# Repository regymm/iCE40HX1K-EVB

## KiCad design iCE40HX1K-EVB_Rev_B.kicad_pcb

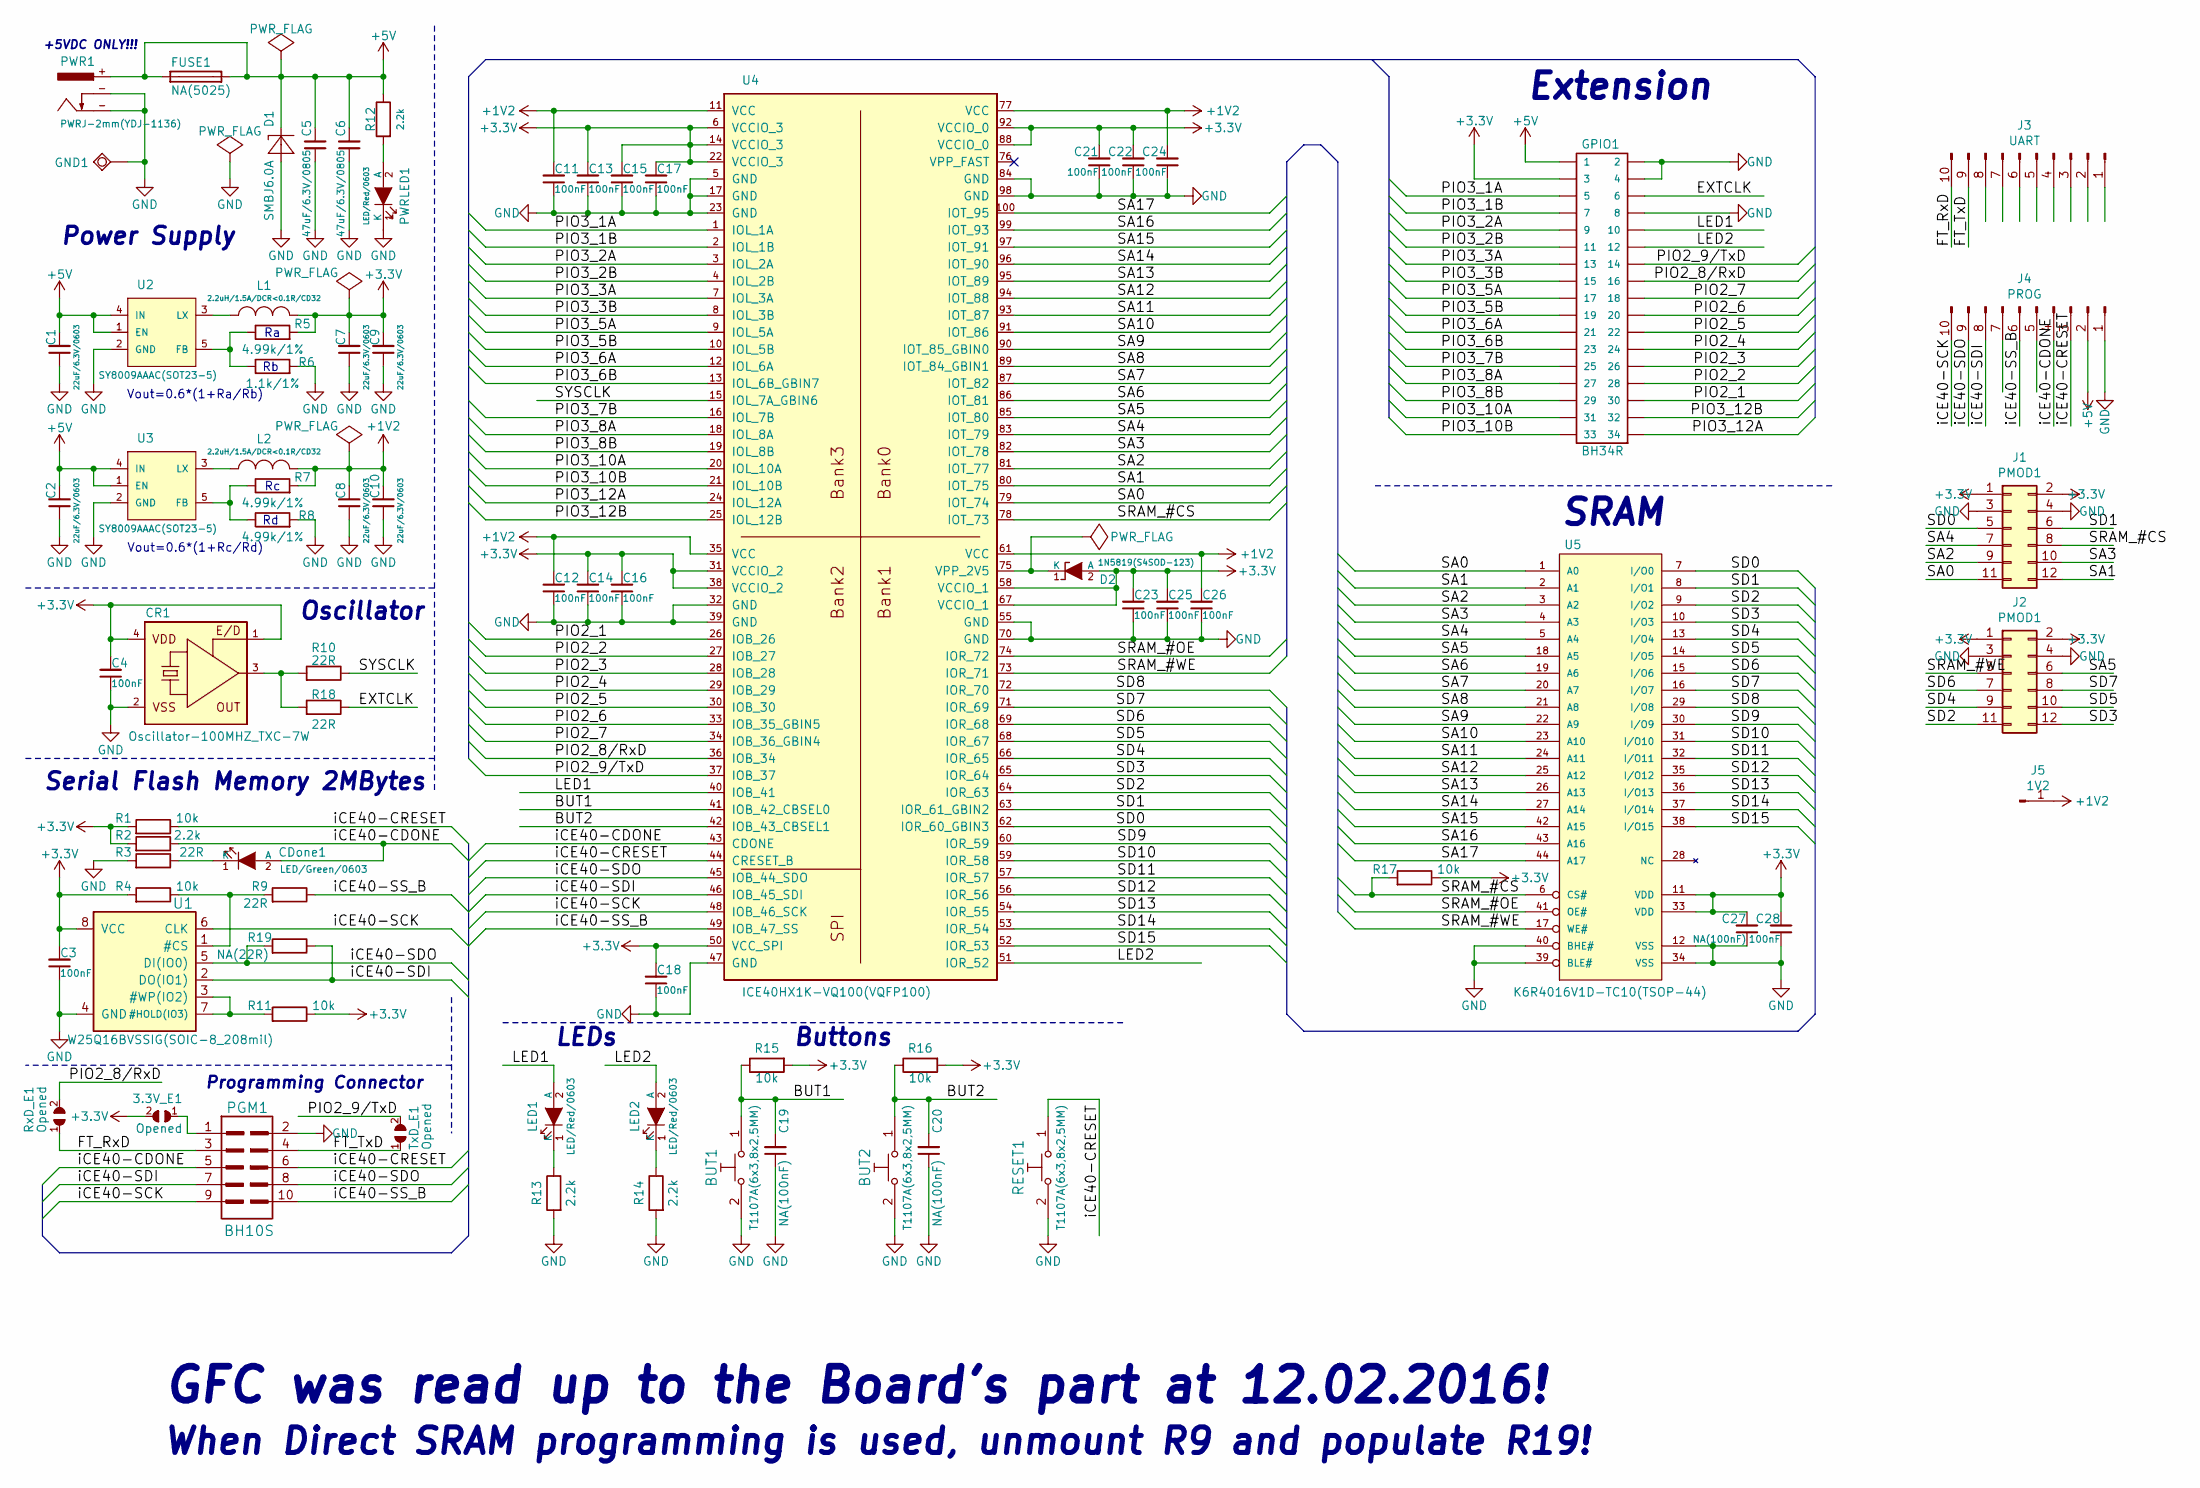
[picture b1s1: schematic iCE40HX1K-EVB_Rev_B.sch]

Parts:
3.3V_E1: Opened; SJ
BUT1, BUT2: T1107A(6x3,8x2,5MM)
C1, C2, C7, C8, C9, C10: 22uF/6.3V/0603; C_0603_5MIL_DWS
C3, C4, C11, C12, C13, C14, C15, C16, C17, C18, C21, C22, C23, C24, C25, C26, C28: 100nF; C_0402_5MIL_DWS
C5, C6: 47uF/6.3V/0805; C_0805_5MIL_DWS
C19, C20, C27: NA(100nF); C_0402_5MIL_DWS
CDone1: LED/Green/0603; LED_0603_KA
CR1: Oscillator-100MHZ_TXC-7W; Crystal_SMD_3225-4Pin_3.2x2.5mm_HandSoldering
D1: SMBJ6.0A; DO214AA
D2: 1N5819(S4SOD-123); SOD-123_1C-2A_KA
FUSE1: NA(5025); FUSE-5025
GND1: TESTPAD; TEST_PAD40x70_SQUARE
GPIO1: BH34R
J1, J2: PMOD1; PinHeader_2x06_P2.54mm_Vertical
J3: UART; PinHeader_1x10_P2.54mm_Vertical
J4: PROG; PinHeader_1x10_P2.54mm_Vertical
J5: 1V2; PinHeader_1x01_P2.54mm_Vertical
L1, L2: 2.2uH/1.5A/DCR<0.1R/CD32; CD32
LED1, LED2: LED/Red/0603; LED_0603_KA
PGM1: BH10S; UEXT_ML10
PWR1: PWRJ-2mm(YDJ-1136)
PWRLED1: LED/Red/0603; LED_0603_KA
R1, R4, R11, R15, R16, R17: 10k; R_0402_5MIL_DWS
R2, R12, R13, R14: 2.2k; R_0402_5MIL_DWS
R3, R9, R10, R18: 22R; R_0402_5MIL_DWS
R5, R7, R8: 4.99k/1%; R_0402_5MIL_DWS
R6: 1.1k/1%; R_0402_5MIL_DWS
R19: NA(22R); R_0402_5MIL_DWS
RESET1: T1107A(6x3,8x2,5MM)
RxD_E1: Opened; SJ
TxD_E1: Opened; SJ
U1: W25Q16BVSSIG(SOIC-8_208mil); SO-8_208mil
U2, U3: SY8009AAAC(SOT23-5); SOT-23-5
U4: ICE40HX1K-VQ100(VQFP100); VQFP100_Pitch-0.5mm_Dimensions-16.00x16.00x1.20mm
U5: K6R4016V1D-TC10(TSOP-44); TSOP-44_Pitch-0.80mm_18.80x11.80x1.20mm

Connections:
+1V2: C8.2, C10.2, C11.2, C12.2, C24.2, C26.2, J5.1, L2.1, R7.2, U4.11 (VCC), U4.35 (VCC), U4.61 (VCC), U4.77 (VCC)
+3V3: 3.3V_E1.2, C3.2, C4.2, C7.2, C9.2, C13.2, C14.2, C15.2, C16.2, C17.2, C18.2, C21.2, C22.2, C23.2, C25.2, C27.2, C28.2, CR1.1 (E/D), CR1.4 (VDD), D2.2 (A), GPIO1.3, J1.1, J1.2, J2.1, J2.2, L1.1, R1.2, R2.2, R4.2, R5.2, R11.1, R15.2, R16.2, R17.1, U1.8 (VCC), U4.6 (VCCIO_3), U4.14 (VCCIO_3), U4.22 (VCCIO_3), U4.31 (VCCIO_2), U4.38 (VCCIO_2), U4.50 (VCC_SPI), U4.58 (VCCIO_1), U4.67 (VCCIO_1), U4.88 (VCCIO_0), U4.92 (VCCIO_0), U5.11 (VDD), U5.33 (VDD)
+5V: C1.2, C2.2, C5.2, C6.2, D1.C, FUSE1.1, FUSE1.2, GPIO1.1, J4.2, PWR1.+, R12.1, U2.1 (EN), U2.4 (IN), U3.1 (EN), U3.4 (IN)
/BUT1: BUT1.1, C19.2, R15.1, U4.41 (IOB_42_CBSEL0)
/BUT2: BUT2.1, C20.2, R16.1, U4.42 (IOB_43_CBSEL1)
/EXTCLK: GPIO1.6, R18.1
/FT_RxD: J3.10, PGM1.3, RxD_E1.1
/FT_TxD: J3.9, PGM1.4, TxD_E1.1
/LED1: GPIO1.10, LED1.2 (A), U4.40 (IOB_41)
/LED2: GPIO1.12, LED2.2 (A), U4.51 (IOR_52)
/PIO2_1: GPIO1.30, U4.26 (IOB_26)
/PIO2_2: GPIO1.28, U4.27 (IOB_27)
/PIO2_3: GPIO1.26, U4.28 (IOB_28)
/PIO2_4: GPIO1.24, U4.29 (IOB_29)
/PIO2_5: GPIO1.22, U4.30 (IOB_30)
/PIO2_6: GPIO1.20, U4.33 (IOB_35_GBIN5)
/PIO2_7: GPIO1.18, U4.34 (IOB_36_GBIN4)
/PIO2_8/RxD: GPIO1.16, RxD_E1.2, U4.36 (IOB_34)
/PIO2_9/TxD: GPIO1.14, TxD_E1.2, U4.37 (IOB_37)
/PIO3_1A: GPIO1.5, U4.1 (IOL_1A)
/PIO3_1B: GPIO1.7, U4.2 (IOL_1B)
/PIO3_2A: GPIO1.9, U4.3 (IOL_2A)
/PIO3_2B: GPIO1.11, U4.4 (IOL_2B)
/PIO3_3A: GPIO1.13, U4.7 (IOL_3A)
/PIO3_3B: GPIO1.15, U4.8 (IOL_3B)
/PIO3_5A: GPIO1.17, U4.9 (IOL_5A)
/PIO3_5B: GPIO1.19, U4.10 (IOL_5B)
/PIO3_6A: GPIO1.21, U4.12 (IOL_6A)
/PIO3_6B: GPIO1.23, U4.13 (IOL_6B_GBIN7)
/PIO3_7B: GPIO1.25, U4.16 (IOL_7B)
/PIO3_8A: GPIO1.27, U4.18 (IOL_8A)
/PIO3_8B: GPIO1.29, U4.19 (IOL_8B)
/PIO3_10A: GPIO1.31, U4.20 (IOL_10A)
/PIO3_10B: GPIO1.33, U4.21 (IOL_10B)
/PIO3_12A: GPIO1.34, U4.24 (IOL_12A)
/PIO3_12B: GPIO1.32, U4.25 (IOL_12B)
/SA0: J1.11, U4.79 (IOT_74), U5.1 (A0)
/SA1: J1.12, U4.80 (IOT_75), U5.2 (A1)
/SA2: J1.9, U4.81 (IOT_77), U5.3 (A2)
/SA3: J1.10, U4.82 (IOT_78), U5.4 (A3)
/SA4: J1.7, U4.83 (IOT_79), U5.5 (A4)
/SA5: J2.6, U4.85 (IOT_80), U5.18 (A5)
/SA6: U4.86 (IOT_81), U5.19 (A6)
/SA7: U4.87 (IOT_82), U5.20 (A7)
/SA8: U4.89 (IOT_84_GBIN1), U5.21 (A8)
/SA9: U4.90 (IOT_85_GBIN0), U5.22 (A9)
/SA10: U4.91 (IOT_86), U5.23 (A10)
/SA11: U4.93 (IOT_87), U5.24 (A11)
/SA12: U4.94 (IOT_88), U5.25 (A12)
/SA13: U4.95 (IOT_89), U5.26 (A13)
/SA14: U4.96 (IOT_90), U5.27 (A14)
/SA15: U4.97 (IOT_91), U5.42 (A15)
/SA16: U4.99 (IOT_93), U5.43 (A16)
/SA17: U4.100 (IOT_95), U5.44 (A17)
/SD0: J1.5, U4.62 (IOR_60_GBIN3), U5.7 (I/O0)
/SD1: J1.6, U4.63 (IOR_61_GBIN2), U5.8 (I/O1)
/SD2: J2.11, U4.64 (IOR_63), U5.9 (I/O2)
/SD3: J2.12, U4.65 (IOR_64), U5.10 (I/O3)
/SD4: J2.9, U4.66 (IOR_65), U5.13 (I/O4)
/SD5: J2.10, U4.68 (IOR_67), U5.14 (I/O5)
/SD6: J2.7, U4.69 (IOR_68), U5.15 (I/O6)
/SD7: J2.8, U4.71 (IOR_69), U5.16 (I/O7)
/SD8: U4.72 (IOR_70), U5.29 (I/O8)
/SD9: U4.60 (IOR_59), U5.30 (I/O9)
/SD10: U4.59 (IOR_58), U5.31 (I/O10)
/SD11: U4.57 (IOR_57), U5.32 (I/O11)
/SD12: U4.56 (IOR_56), U5.35 (I/O12)
/SD13: U4.54 (IOR_55), U5.36 (I/O13)
/SD14: U4.53 (IOR_54), U5.37 (I/O14)
/SD15: U4.52 (IOR_53), U5.38 (I/O15)
/SRAM_#CS: J1.8, R17.2, U4.78 (IOT_73), U5.6 (CS#)
/SRAM_#OE: U4.74 (IOR_72), U5.41 (OE#)
/SRAM_#WE: J2.5, U4.73 (IOR_71), U5.17 (WE#)
/SYSCLK: R10.1, U4.15 (IOL_7A_GBIN6)
/iCE40-CDONE: CDone1.2 (A), J4.4, PGM1.5, R2.1, U4.43 (CDONE)
/iCE40-CRESET: J4.3, PGM1.6, R1.1, RESET1.1, U4.44 (CRESET_B)
/iCE40-SCK: J4.10, PGM1.9, U1.6 (CLK), U4.48 (IOB_46_SCK)
/iCE40-SDI: J4.8, PGM1.7, R19.1, U1.2 (DO(IO1)), U4.46 (IOB_45_SDI)
/iCE40-SDO: J4.9, PGM1.8, R19.2, U1.5 (DI(IO0)), U4.45 (IOB_44_SDO)
/iCE40-SS_B: J4.6, PGM1.10, R9.1, U4.49 (IOB_47_SS)
GND: BUT1.2, BUT2.2, C1.1, C2.1, C3.1, C4.1, C5.1, C6.1, C7.1, C8.1, C9.1, C10.1, C11.1, C12.1, C13.1, C14.1, C15.1, C16.1, C17.1, C18.1, C19.1, C20.1, C21.1, C22.1, C23.1, C24.1, C25.1, C26.1, C27.1, C28.1, CR1.2 (VSS), D1.A, GND1.1, GPIO1.2, GPIO1.4, GPIO1.8, J1.3, J1.4, J2.3, J2.4, J4.1, PGM1.2, PWR1.-, PWRLED1.1 (K), R3.2, R6.2, R8.2, R13.2, R14.2, RESET1.2, U1.4 (GND), U2.2 (GND), U3.2 (GND), U4.5 (GND), U4.17 (GND), U4.23 (GND), U4.32 (GND), U4.39 (GND), U4.47 (GND), U4.55 (GND), U4.70 (GND), U4.84 (GND), U4.98 (GND), U5.12 (VSS), U5.34 (VSS), U5.39 (BLE#), U5.40 (BHE#)
unnamed: 3.3V_E1.1, PGM1.1
unnamed: CDone1.1 (K), R3.1
unnamed: CR1.3 (OUT), R10.2, R18.2
unnamed: D2.1 (K), U4.75 (VPP_2V5)
unnamed: L1.2, U2.3 (LX)
unnamed: L2.2, U3.3 (LX)
unnamed: LED1.1 (K), R13.1
unnamed: LED2.1 (K), R14.1
unnamed: PWRLED1.2 (A), R12.2
unnamed: R4.1, R9.2, U1.1 (#CS)
unnamed: R5.1, R6.1, U2.5 (FB)
unnamed: R7.1, R8.1, U3.5 (FB)
unnamed: R11.2, U1.3 (#WP(IO2)), U1.7 (#HOLD(IO3))

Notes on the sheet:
Power Supply
Vout=0.6*(1+Ra/Rb)
Extension
GFC was read up to the Board's part at 12.02.2016!
+5VDC ONLY!!!
Vout=0.6*(1+Rc/Rd)
SRAM
Oscillator
Serial Flash Memory 2MBytes
Programming Connector
LEDs
Buttons
When Direct SRAM programming is used, unmount R9 and populate R19!

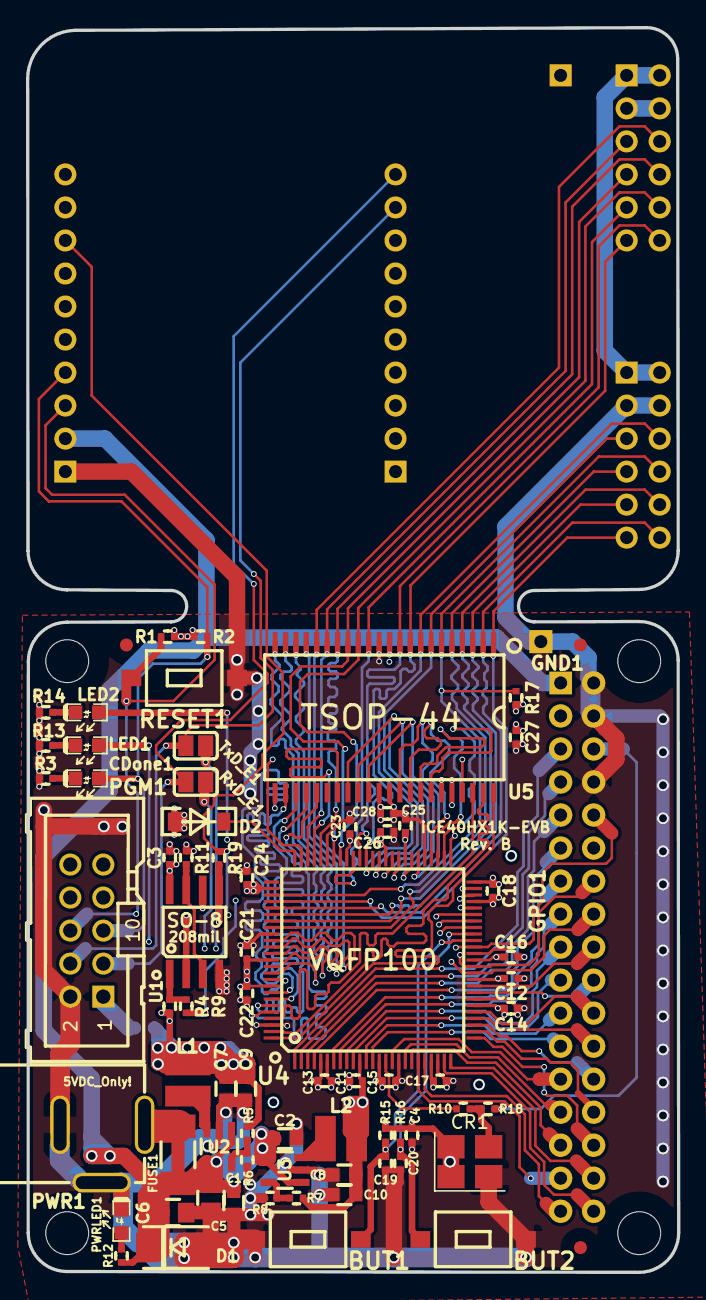
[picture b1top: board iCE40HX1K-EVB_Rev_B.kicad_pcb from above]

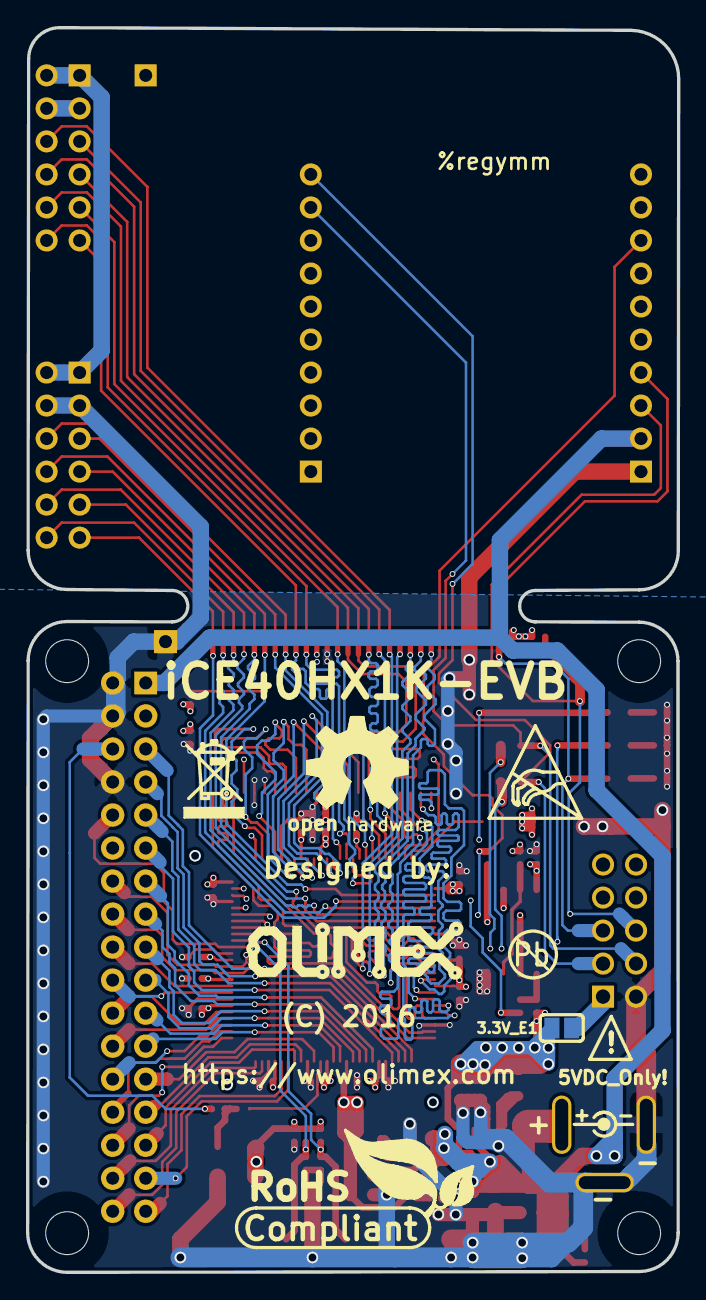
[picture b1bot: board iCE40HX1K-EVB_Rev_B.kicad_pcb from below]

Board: 4 copper layers, 50.1 x 95.7 mm, 83 parts (3 on the bottom side), 94 nets.

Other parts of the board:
MountingHole: Mounting_hole_3.3mm
MountingHole#2, MountingHole#3, MountingHole#4: Mounting_hole_3.3mm
Ref**: Val**; LOGO_ANTISTATIC_1
Ref**#2: Val**; LOGO_ROHS_1

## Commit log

2021-09-30 regymm modified version

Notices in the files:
iCE40HX1K-EVB_Rev_B.kicad_pcb:
(C) 2016
